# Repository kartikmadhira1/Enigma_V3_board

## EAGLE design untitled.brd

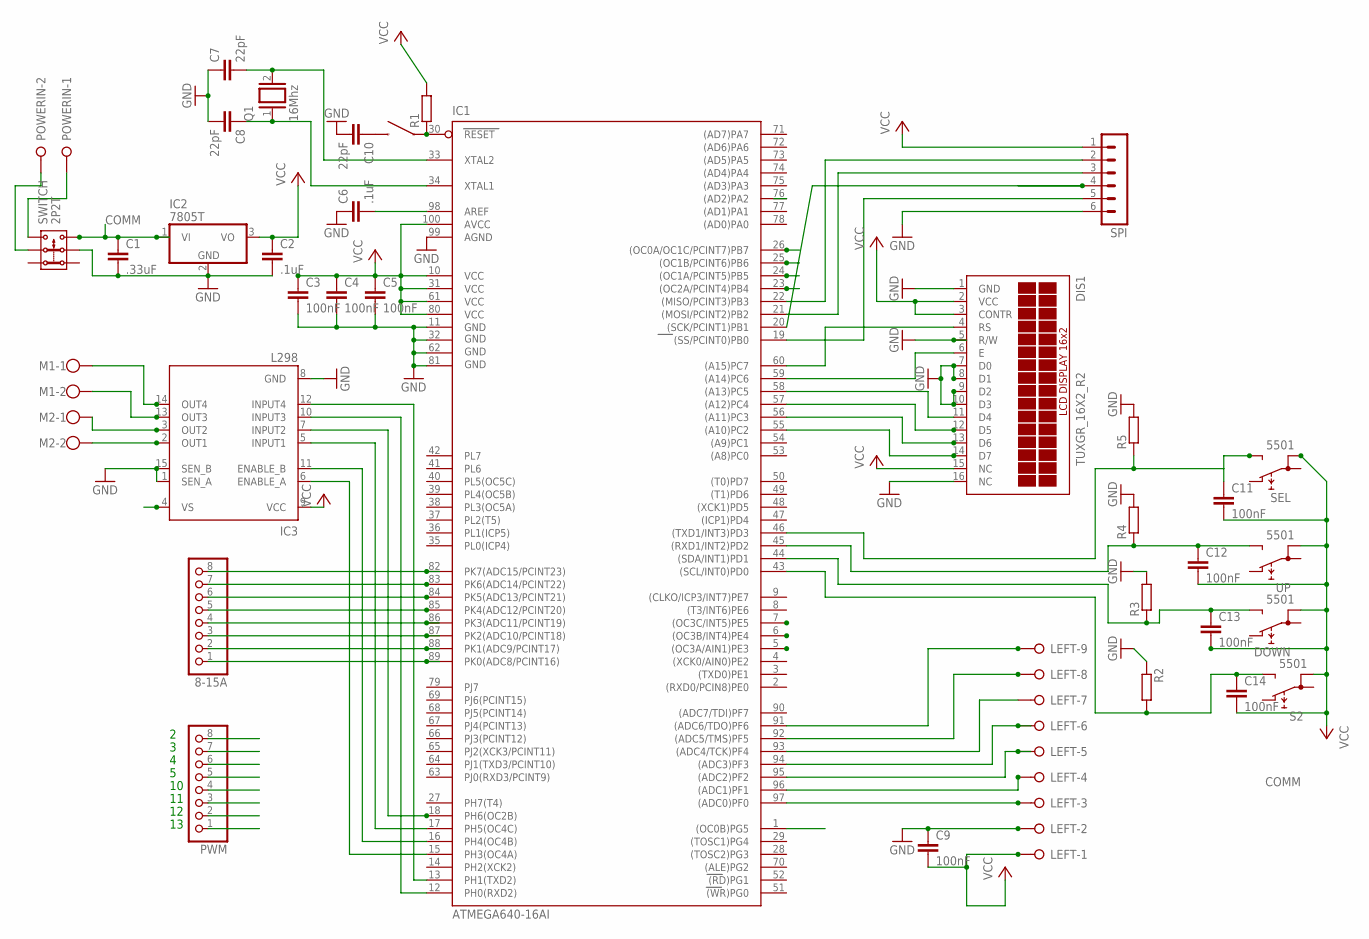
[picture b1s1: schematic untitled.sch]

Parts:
8-15A: PINHD-1X8; 1X08
C1: .33uF; C0805
C2, C6: .1uF; C0805
C3, C4, C5, C9, C11, C12, C13, C14: 100nF; C0805
C7, C8, C10: 22pF; C0805
DIS1: TUXGR_16X2_R2
DOWN: 5501
IC1: ATMEGA640-16AI; TQFP100
IC2: 7805T; TO220H
IC3: L298; MULTIWATT-15
LEFT: W237-09P; W237-9P
M1, M2: W237-102
POWERIN: W237-02P; W237-132
PWM: PINHD-1X8; 1X08
Q1: 16Mhz; QS
R1, R2, R3, R4, R5: R; R0805
S2: 5501
SEL: 5501
SPI: MA06-1
SWITCH: 2P2T
U$1: TACT-SWITCH-40-40; 40-40
UP: 5501

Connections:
2: IC1.6 ((OC3B/INT4)PE4), PWM.8
3: IC1.7 ((OC3C/INT5)PE5), PWM.7
4: IC1.1 ((OC0B)PG5), PWM.6
5: IC1.5 ((OC3A/AIN1)PE3), PWM.5
10: IC1.23 ((OC2A/PCINT4)PB4), PWM.4
11: IC1.24 ((OC1A/PCINT5)PB5), PWM.3
12: IC1.25 ((OC1B/PCINT6)PB6), PWM.2
13: IC1.26 ((OC0A/OC1C/PCINT7)PB7), PWM.1
24: IC1.76 ((AD2)PA2)
COMM: C1.1, IC2.1 (VI), IC3.4 (VS), SWITCH.3.2
GND: C1.2, C2.2, C3.2, C4.2, C5.2, C6.1, C7.1, C8.2, C9.1, C10.2, DIS1.1 (GND), DIS1.5 (R/W), DIS1.7 (D0), DIS1.8 (D1), DIS1.9 (D2), DIS1.10 (D3), DIS1.16 (NC), IC1.11 (GND), IC1.32 (GND1), IC1.62 (GND2), IC1.81 (GND3), IC1.99 (AGND), IC2.2 (GND), IC3.1 (SEN_A), IC3.8 (GND), IC3.15 (SEN_B), LEFT.2, R2.1, R3.2, R4.2, R5.2, SPI.6, SWITCH.2.2
unnamed: POWERIN.1, SWITCH.3.1
unnamed: IC3.13 (OUT3), M1.2
unnamed: IC3.14 (OUT4), M1.1
unnamed: IC3.2 (OUT1), M2.2
unnamed: IC3.3 (OUT2), M2.1
unnamed: POWERIN.2, SWITCH.2.1
unnamed: C6.2, IC1.98 (AREF)
unnamed: C7.2, IC1.33 (XTAL2), Q1.2
unnamed: C8.1, IC1.34 (XTAL1), Q1.1
unnamed: IC1.97 ((ADC0)PF0), LEFT.3
unnamed: C10.1, U$1.1, U$1.2
unnamed: IC1.96 ((ADC1)PF1), LEFT.4
unnamed: IC1.95 ((ADC2)PF2), LEFT.5
unnamed: IC1.94 ((ADC3)PF3), LEFT.6
unnamed: IC1.93 ((ADC4/TCK)PF4), LEFT.7
unnamed: IC1.92 ((ADC5/TMS)PF5), LEFT.8
unnamed: IC1.91 ((ADC6/TDO)PF6), LEFT.9
unnamed: DIS1.4 (RS), IC1.60 ((A15)PC7)
unnamed: DIS1.6 (E), IC1.59 ((A14)PC6)
unnamed: DIS1.11 (D4), IC1.58 ((A13)PC5)
unnamed: DIS1.12 (D5), IC1.57 ((A12)PC4)
unnamed: DIS1.13 (D6), IC1.56 ((A11)PC3)
unnamed: DIS1.14 (D7), IC1.55 ((A10)PC2)
unnamed: IC1.15 (PH3(OC4A)), IC3.6 (ENABLE_A)
unnamed: IC1.16 (PH4(OC4B)), IC3.11 (ENABLE_B)
unnamed: IC1.17 (PH5(OC4C)), IC3.5 (INPUT1)
unnamed: IC1.18 (PH6(OC2B)), IC3.7 (INPUT2)
unnamed: IC1.12 (PH0(RXD2)), IC3.10 (INPUT3)
unnamed: IC1.13 (PH1(TXD2)), IC3.12 (INPUT4)
unnamed: IC1.30 (RESET), R1.1, U$1.3, U$1.4
unnamed: IC1.22 ((MISO/PCINT3)PB3), SPI.2
unnamed: IC1.21 ((MOSI/PCINT2)PB2), SPI.3
unnamed: IC1.20 ((SCK/PCINT1)PB1), SPI.4
unnamed: IC1.19 ((SS/PCINT0)PB0), SPI.5
unnamed: C14.1, IC1.43 ((SCL/INT0)PD0), R2.2, S2.NO
unnamed: C13.1, DOWN.NO, IC1.44 ((SDA/INT1)PD1), R3.1
unnamed: C12.1, IC1.45 ((RXD1/INT2)PD2), R4.1, UP.NO
unnamed: C11.1, IC1.46 ((TXD1/INT3)PD3), R5.1, SEL.NO
unnamed: 8-15A.8, IC1.82 (PK7(ADC15/PCINT23))
unnamed: 8-15A.7, IC1.83 (PK6(ADC14/PCINT22))
unnamed: 8-15A.6, IC1.84 (PK5(ADC13/PCINT21))
unnamed: 8-15A.5, IC1.85 (PK4(ADC12/PCINT20))
unnamed: 8-15A.4, IC1.86 (PK3(ADC11/PCINT19))
unnamed: 8-15A.3, IC1.87 (PK2(ADC10/PCINT18))
unnamed: 8-15A.2, IC1.88 (PK1(ADC9/PCINT17))
unnamed: 8-15A.1, IC1.89 (PK0(ADC8/PCINT16))
VCC: C2.1, C3.1, C4.1, C5.1, C9.2, C11.2, C12.2, C13.2, C14.2, DIS1.2 (VCC), DIS1.3 (CONTR), DIS1.15 (NC), DOWN.1B, IC1.10 (VCC), IC1.31 (VCC1), IC1.61 (VCC2), IC1.80 (VCC3), IC1.100 (AVCC), IC2.3 (VO), IC3.9 (VCC), LEFT.1, R1.2, S2.1B, SEL.1B, SPI.1, UP.1B

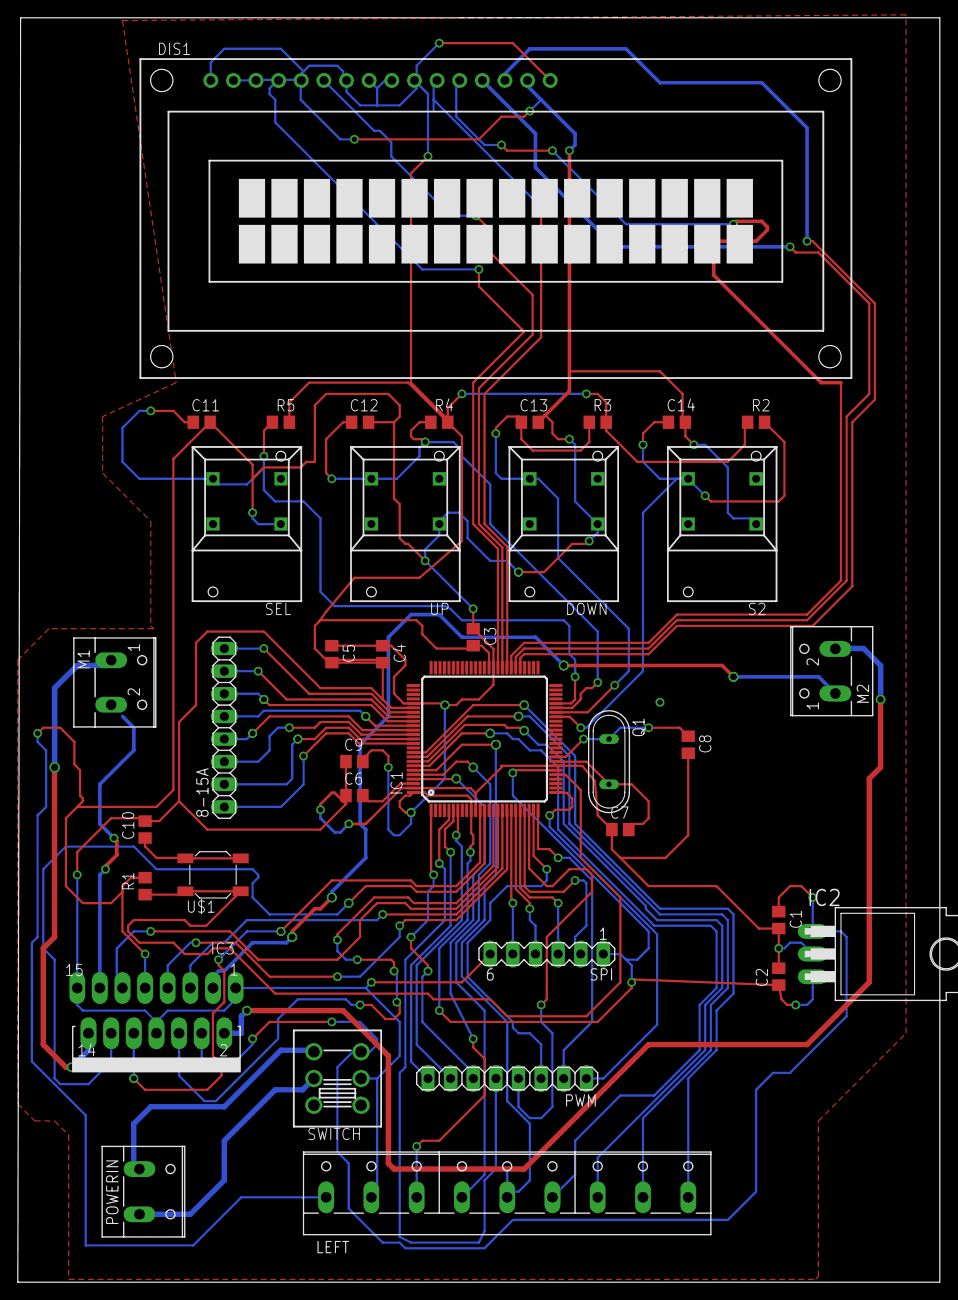
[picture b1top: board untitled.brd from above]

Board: 2 copper layers, 103.5 x 141.9 mm, 37 parts (0 on the bottom side), 57 nets.

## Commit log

2017-01-15 Board files for the V3 version
